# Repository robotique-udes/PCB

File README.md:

# PCB

Cette repo regroupe les fichiers et projets de PCB de tous les sous-groupe de robotique UdeS. Chaque groupe s'organise dans son dossier. Dans le futur il serait pertinent de monter une librairie de Symbole et de Footprint globale entre les groupes.

## Protection de branches:

- Seulement les branches nommées avec ce pattern sont acceptées:
  - rover/**
  - exo/**

- Une Pull Request est requise pour pouvoir merge dans le main

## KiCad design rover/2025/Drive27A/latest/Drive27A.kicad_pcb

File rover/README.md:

# PCB

Ce répertoire contient les projets du rover, les projets sont trié par version du rover:

| Compétition | Surnom du rover | Nom                                                |
|-------------|-----------------|----------------------------------------------------|
| CIRC 2024   | T_REX           | Teleoperated Rover for Extraterrestrial Xploration |

Les footprints custom locaux seront pour l'instant enregistrés à l'intérieur des projets pour simplifier la gestion. Dans le futur, une bibliothèque globale pourrait être créée.

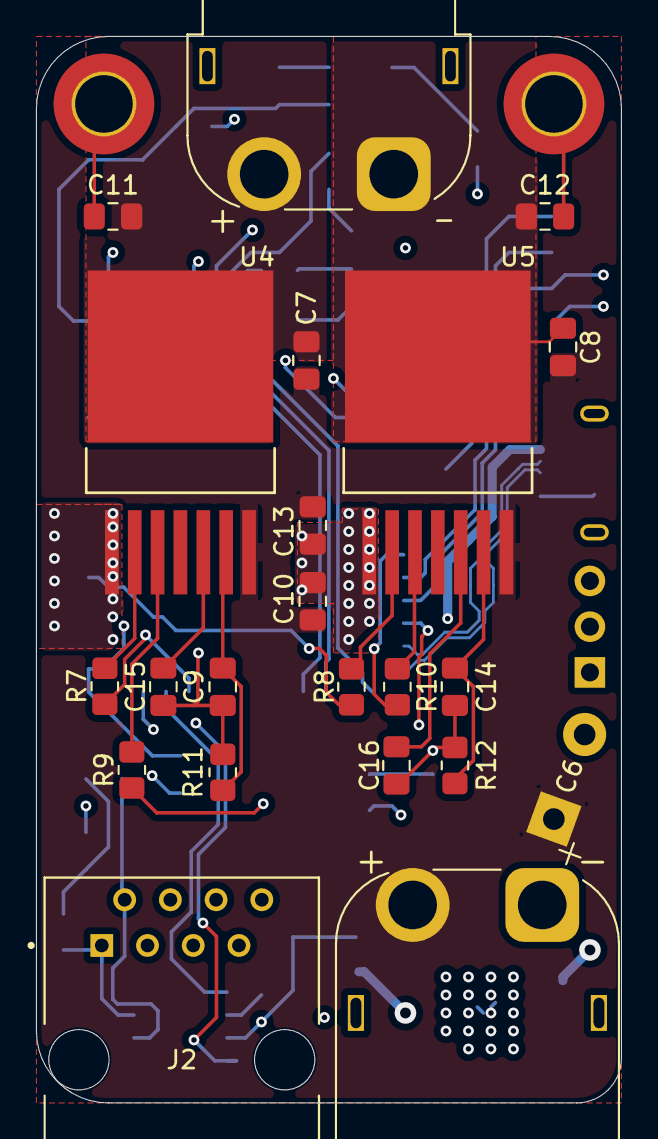
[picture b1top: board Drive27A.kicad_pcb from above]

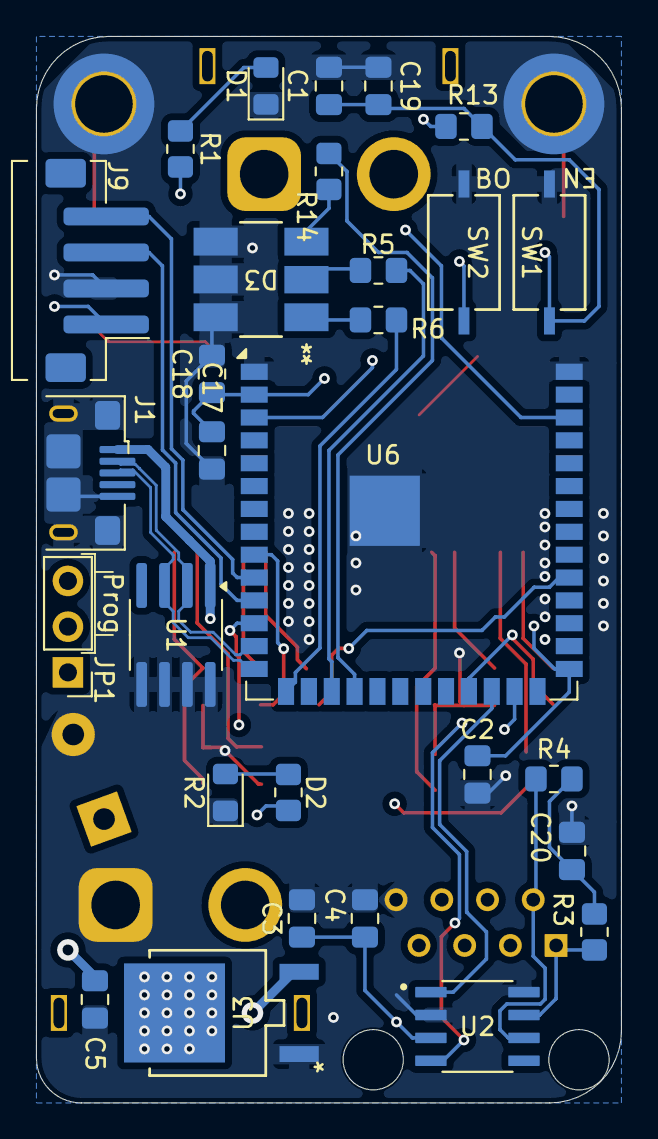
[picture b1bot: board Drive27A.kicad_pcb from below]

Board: 4 copper layers, 32.5 x 59.3 mm, 53 parts (29 on the bottom side), 40 nets.

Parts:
C1, C2, C4, C10, C13, C15, C16, C18: 100nF; C_0805_2012Metric_Pad1.18x1.45mm_HandSolder
C3, C5: 10uF; C_0805_2012Metric_Pad1.18x1.45mm_HandSolder
C6: 470uF; CP_Radial_D12.5mm_P5.00mm
C7, C8, C11, C12: 220nF; C_0805_2012Metric_Pad1.18x1.45mm_HandSolder
C9, C14: 1nF; C_0805_2012Metric_Pad1.18x1.45mm_HandSolder
C17: 22uF; C_0805_2012Metric_Pad1.18x1.45mm_HandSolder
C19: 1uF; C_0805_2012Metric_Pad1.18x1.45mm_HandSolder
C20: 47nF; C_0805_2012Metric_Pad1.18x1.45mm_HandSolder
D1, D2: R; LED_0805_2012Metric_Pad1.15x1.40mm_HandSolder
D3: CLP6C-FKB-CKNPRGJBB7A363; CLP6C-FKB-CKNPRGJBB7A363_CRE
H1, H2: MountingHole_Pad; MountingHole_3.2mm_M3_DIN965_Pad_TopBottom
J1: USB_B_Micro; USB_Micro-B_Amphenol_10118193-0001LF_Horizontal
J2: RJ45; AMPHENOL_54601-908WPLF
J6: XT60PW-M; AMASS_XT60PW-M_1x02_P7.20mm_Horizontal
J7: XT60PW-F; AMASS_XT60PW-F_1x02_P7.20mm_Horizontal
J9: B4B-XH-A_LF__SN_; JST_PH_B4B-PH-SM4-TB_1x04-1MP_P2.00mm_Vertical
JP1: Jumper_3_Open; PinHeader_1x03_P2.54mm_Vertical
R1, R2, R5, R6, R11, R12, R14: 1k; R_0805_2012Metric_Pad1.20x1.40mm_HandSolder
R3, R4: 60; R_0805_2012Metric_Pad1.20x1.40mm_HandSolder
R7, R8, R9, R10, R13: 10k; R_0805_2012Metric_Pad1.20x1.40mm_HandSolder
SW1, SW2: TS09-63-25-WT-160-SMT-TR; SW_TS09-63-25_CUD
U1: SOIC-8-1EP_3.9x4.9mm_P1.27mm_EP2.29x3mm
U2: SN65HVD232Q; SOIC127P600X175-8N
U3: LD1086DT33TR; TO252-2_AZ1117ID-3.3TRG1_DIO-L
U4, U5: BTN8962TA; PG-TO263-7-1_INF-M
U6: ESP32-S3-WROOM-1

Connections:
+3.3V: C3.1, C4.1, C17.1, C18.1, J9.1, R2.2, R13.1, U2.3 (VCC), U3.2 (OUTPUT), U6.2 (3V3)
+5V: J1.1 (VBUS), JP1.3 (B), U1.1
+24V: C6.1, C7.1, C8.1, C10.1, C13.1, J6.2 (+), U4.7 (VS), U5.7 (VS)
+24V_Logic: J2.7, JP1.1 (A)
CANH: J2.1, R3.2, U2.7 (CANH)
CANL: J2.2, R4.1, U2.6 (CANL)
ENC_QUAD_A: J9.3, U6.11 (IO18)
ENC_QUAD_B: J9.4, U6.10 (IO17)
EN_PB: C1.2, C19.1, R13.2, SW1.2, U6.3 (EN)
GND: C1.1, C2.1, C3.2, C4.2, C5.2, C6.2, C9.2, C10.2, C11.2, C12.2, C13.2, C14.2, C15.2, C16.2, C17.2, C18.2, C19.2, C20.1, D1.1 (K), D2.1 (K), D3.4, D3.5, D3.6, H1.1, H2.1, J1.5 (GND), J1.6 (Shield), J2.8, J6.1 (-), J9.2, R11.2, R12.2, SW1.1, SW2.1, U1.5, U1.6, U1.7, U1.8, U2.2 (GND), U2.8 (S), U3.1 (GND), U4.1 (GND), U5.1 (GND), U6.1 (GND), U6.40 (GND), U6.41 (GND)
GPIO_0: C2.2, SW2.2, U6.27 (IO0)
J2+: C7.2, C11.1, J7.2 (+), U4.8 (OUT)
J2-: C8.2, C12.1, J7.1 (-), U5.8 (OUT)
J2_EN_1: R9.2, U6.12 (IO8)
J2_EN_2: R10.2, U6.9 (IO16)
J2_IN_1: R7.2, U6.23 (IO21)
J2_IN_2: R8.2, U6.31 (IO38)
LED_B: R14.2, U6.18 (IO10)
LED_BUILDIN: R1.2, U6.38 (IO2)
LED_G: R5.2, U6.17 (IO9)
LED_R: R6.2, U6.15 (IO3)
unnamed: C20.2, R3.1, R4.2
unnamed: D1.2 (A), R1.1
unnamed: D2.2 (A), R2.1
unnamed: D3.1, R6.1
unnamed: D3.2, R5.1
unnamed: D3.3, R14.1
unnamed: C5.1, JP1.2 (C), U3.3 (INPUT)
unnamed: R9.1, U4.3 (EN_(INH))
unnamed: R7.1, U4.2 (IN)
unnamed: C9.1, R11.1, U4.6 (IS)
unnamed: C15.1, U4.5 (SR)
unnamed: R10.1, U5.3 (EN_(INH))
unnamed: R8.1, U5.2 (IN)
unnamed: C14.1, R12.1, U5.6 (IS)
unnamed: C16.1, U5.5 (SR)
RXC: U2.1 (TXD), U6.24 (IO47)
TXC: U2.4 (RXD), U6.25 (IO48)
USB_N: J1.2 (D-), U1.2, U6.13 (IO19)
USB_P: J1.3 (D+), U1.3, U6.14 (IO20)

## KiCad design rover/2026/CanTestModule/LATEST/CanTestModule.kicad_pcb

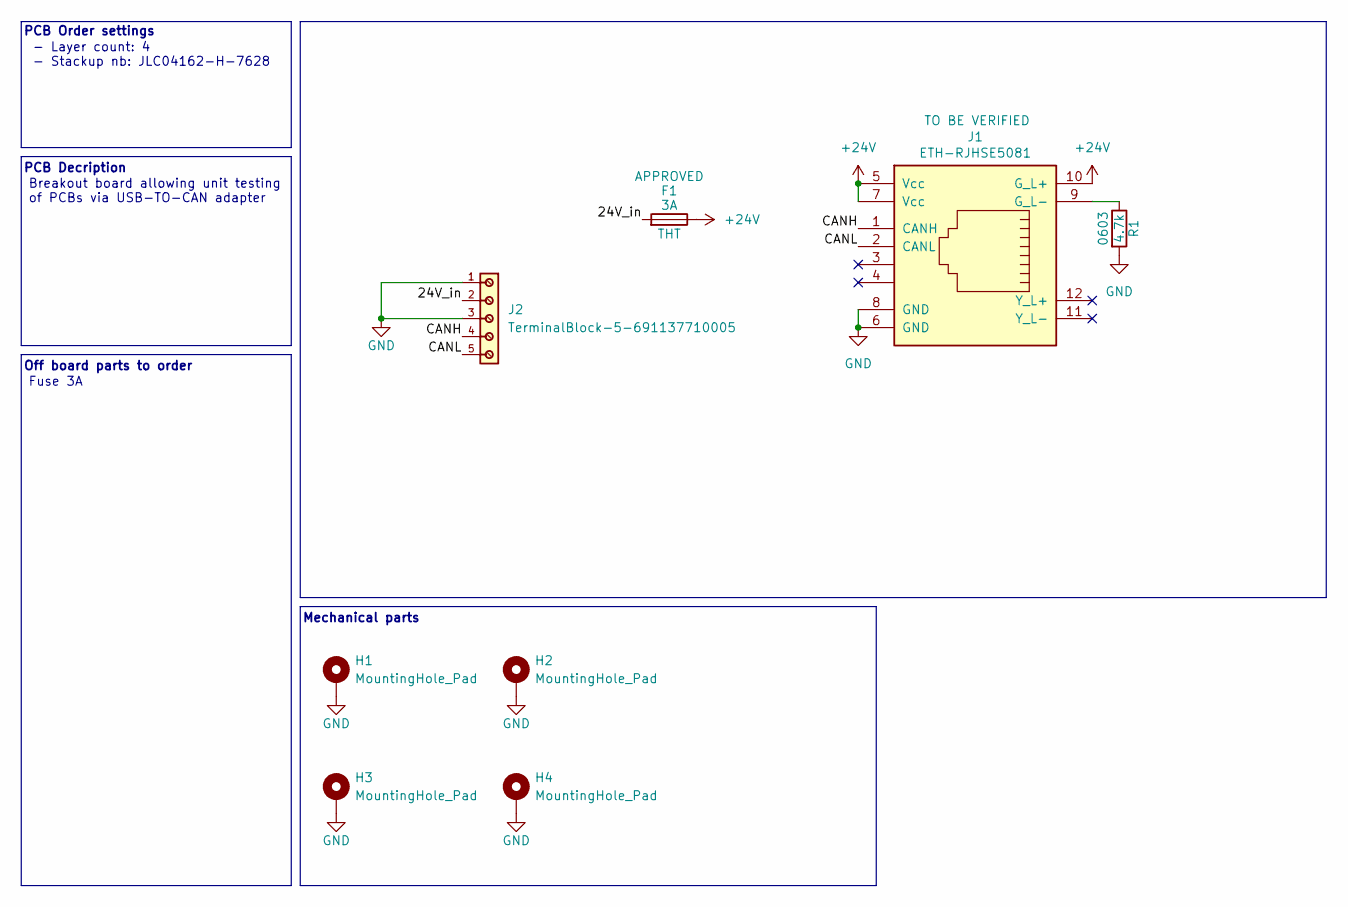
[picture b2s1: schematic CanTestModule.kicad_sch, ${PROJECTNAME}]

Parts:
F1: 3A; FUSE_3568-20
H1, H2, H3, H4: MountingHole_Pad; MountingHole_3.2mm_M3_DIN965_Pad_TopBottom
J1: ETH-RJHSE5081
J2: TerminalBlock-5-691137710005; TerminalBlock-5_P5.00mm-691137710005
R1: 4.7k; R_0603_1608Metric_Pad0.98x0.95mm_HandSolder

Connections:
+24V: F1.2, J1.5 (Vcc), J1.7 (Vcc), J1.10 (G_L+)
/24V_in: F1.1, J2.2
/CANH: J1.1 (CANH), J2.4
/CANL: J1.2 (CANL), J2.5
GND: H1.1 (1_1), H2.1 (1_1), H3.1 (1_1), H4.1 (1_1), J1.6 (GND), J1.8 (GND), J2.1, J2.3, R1.2
unnamed: J1.9 (G_L-), R1.1

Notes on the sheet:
Off board parts to order
Mechanical parts
- Layer count: 4 - Stackup nb: JLC04162-H-7628
PCB Decription
PCB Order settings
Breakout board allowing unit testing of PCBs via USB-TO-CAN adapter
Fuse 3A

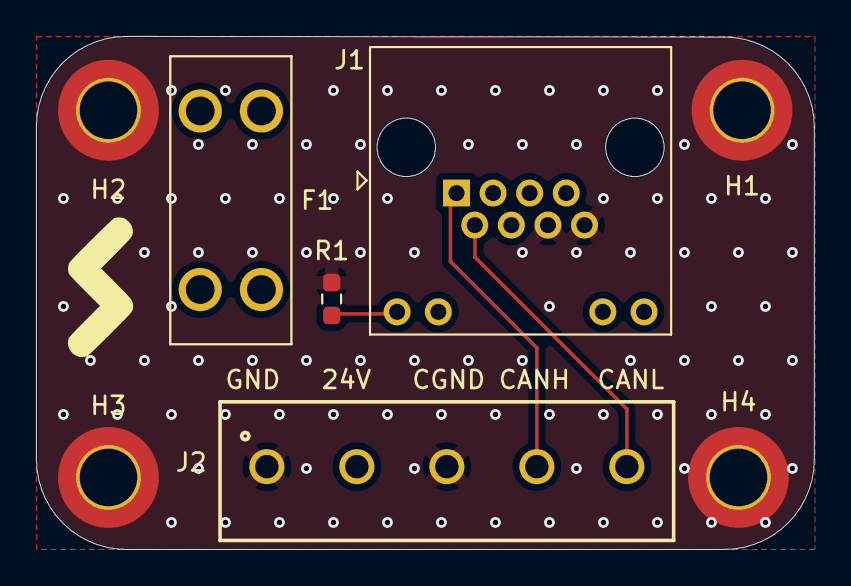
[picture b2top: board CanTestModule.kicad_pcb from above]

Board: 4 copper layers, 43.2 x 28.5 mm, 8 parts (0 on the bottom side), 6 nets.

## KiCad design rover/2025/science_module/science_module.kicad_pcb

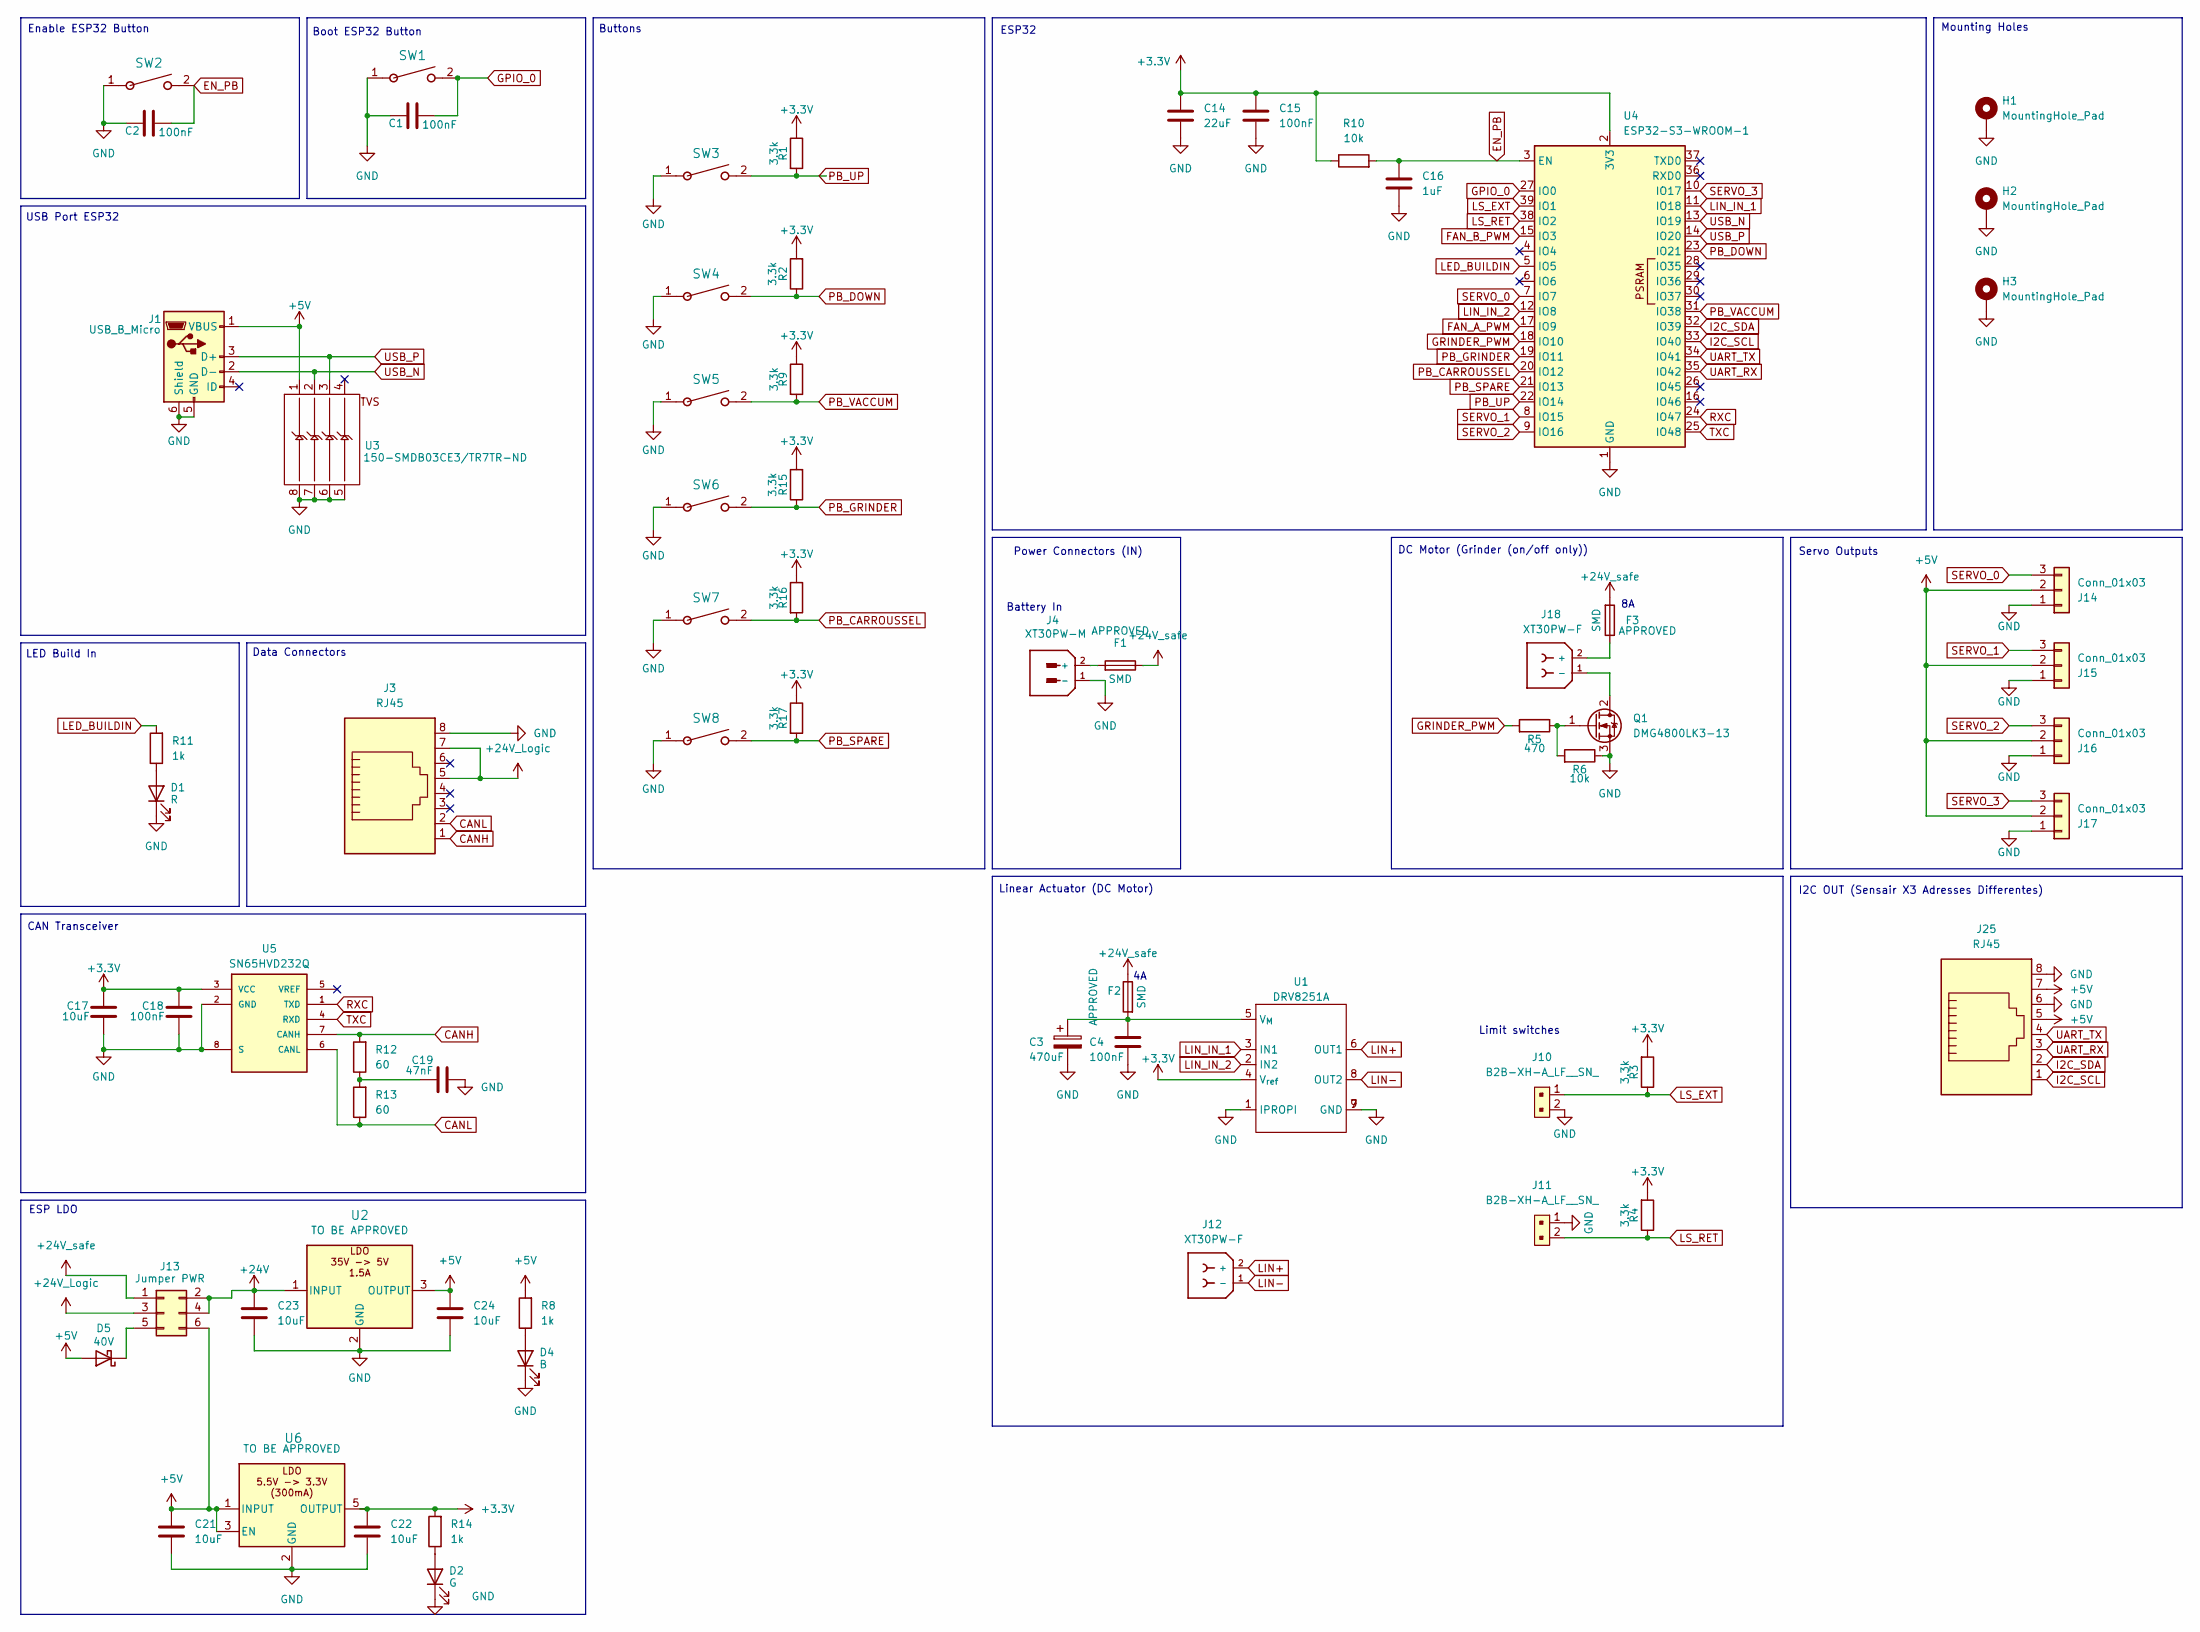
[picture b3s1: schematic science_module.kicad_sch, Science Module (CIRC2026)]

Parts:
C1, C2, C4, C15, C18: 100nF; C_0805_2012Metric_Pad1.18x1.45mm_HandSolder
C3: 470uF; CP_Radial_D8.0mm_P3.50mm
C14: 22uF; C_0805_2012Metric_Pad1.18x1.45mm_HandSolder
C16: 1uF; C_0805_2012Metric_Pad1.18x1.45mm_HandSolder
C17, C21, C22, C23, C24: 10uF; C_0805_2012Metric_Pad1.18x1.45mm_HandSolder
C19: 47nF; C_0805_2012Metric_Pad1.18x1.45mm_HandSolder
D1: R; LED_0805_2012Metric_Pad1.15x1.40mm_HandSolder
D2: G; LED_0805_2012Metric_Pad1.15x1.40mm_HandSolder
D4: B; LED_0805_2012Metric_Pad1.15x1.40mm_HandSolder
D5: 40V; D_SMA
F1, F2, F3: FuseHolder-3588-20
H1, H2, H3: MountingHole_Pad; MountingHole_3.2mm_M3_DIN965_Pad_TopBottom
J1: USB_B_Micro; USB_Micro-B_Amphenol_10118193-0001LF_Horizontal
J3, J25: RJ45; ASSMANN_A-2014-2-4-N-T-R
J4: XT30PW-M; AMASS_XT60PW-M_1x02_P7.20mm_Horizontal; PARTREV 1.2
J10, J11: B2B-XH-A_LF__SN_; JST_XH_B2B-XH-A_1x02_P2.50mm_Vertical; MPN B2B-XH-A(LF)(SN); Digi-Key_PN 455-2247-ND
J12, J18: XT30PW-F; AMASS_XT30PW-F_1x02_P2.50mm_Horizontal; PARTREV 1.2
J13: Jumper PWR; PinHeader_2x03_P2.54mm_Vertical
J14, J15, J16, J17: Conn_01x03; PinHeader_1x03_P2.54mm_Vertical
Q1: DMG4800LK3-13; TO-252-2
R1, R2, R3, R4, R9, R15, R16, R17: 3.3k; R_0805_2012Metric_Pad1.20x1.40mm_HandSolder
R5: 470; R_0805_2012Metric_Pad1.20x1.40mm_HandSolder
R6, R10: 10k; R_0805_2012Metric_Pad1.20x1.40mm_HandSolder
R8, R11, R14: 1k; R_0805_2012Metric_Pad1.20x1.40mm_HandSolder
R12, R13: 60; R_0805_2012Metric_Pad1.20x1.40mm_HandSolder
SW1, SW2, SW3, SW4, SW5, SW6, SW7, SW8: TS09-63-25-WT-160-SMT-TR; SW_TS09-63-25_CUD
U1: DRV8251A; Texas_HSOP-8-1EP_3.9x4.9mm_P1.27mm_ThermalVias
U2: LDO-LM7805MPX/NOPB; TO-263-3_TabPin2
U3: 150-SMDB03CE3/TR7TR-ND; SOIC-8-1EP_3.9x4.9mm_P1.27mm_EP2.29x3mm
U4: ESP32-S3-WROOM-1
U5: SN65HVD232Q; SOIC127P600X175-8N; PARTREV 4
U6: LDO-TLV74033PDBVR; SOT-23-5_HandSoldering

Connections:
+3.3V: C14.1, C15.1, C17.1, C18.1, C22.1, R1.1, R2.2, R3.2, R4.2, R9.1, R10.1, R14.2, R15.2, R16.1, R17.1, U1.4 (V_{ref}), U4.2 (3V3), U5.3 (VCC), U6.5 (OUTPUT)
+5V: C21.1, C24.1, D5.2 (A), J1.1 (VBUS), J13.6, J14.2, J15.2, J16.2, J17.2, J25.5, J25.7, R8.2, U2.3 (OUTPUT), U3.1, U6.1 (INPUT), U6.3 (EN)
+24V: C23.1, J13.2, J13.4, U2.1 (INPUT)
+24V_Logic: J3.5, J3.7, J13.3
+24V_safe: F1.2, F2.2, F3.1, J13.1
CANH: J3.1, R12.2, U5.7 (CANH)
CANL: J3.2, R13.1, U5.6 (CANL)
EN_PB: C2.2, C16.1, R10.2, SW2.2, U4.3 (EN)
FAN_A_PWM: U4.17 (IO9)
FAN_B_PWM: U4.15 (IO3)
GND: C1.1, C2.1, C3.2, C4.2, C14.2, C15.2, C16.2, C17.2, C18.2, C19.1, C21.2, C22.2, C23.2, C24.2, D1.1 (K), D2.1 (K), D4.1 (K), H1.1 (1_1), H2.1 (1_1), H3.1 (1_1), J1.5 (GND), J1.6 (Shield), J3.8, J4.1 (-), J10.2, J11.1, J14.1, J15.1, J16.1, J17.1, J25.6, J25.8, Q1.3 (S), R6.1, SW1.1, SW2.1, SW3.1, SW4.1, SW5.1, SW6.1, SW7.1, SW8.1, U1.1 (IPROPI), U1.7 (GND), U1.9 (GND), U2.2 (GND), U3.5, U3.6, U3.7, U3.8, U4.1 (GND), U4.40 (GND), U4.41 (GND), U5.2 (GND), U5.8 (S), U6.2 (GND)
GPIO_0: C1.2, SW1.2, U4.27 (IO0)
GRINDER_PWM: R5.2, U4.18 (IO10)
I2C_SCL: J25.1, U4.33 (IO40)
I2C_SDA: J25.2, U4.32 (IO39)
LED_BUILDIN: R11.2, U4.5 (IO5)
LIN+: J12.2 (+), U1.6 (OUT1)
LIN-: J12.1 (-), U1.8 (OUT2)
LIN_IN_1: U1.3 (IN1), U4.11 (IO18)
LIN_IN_2: U1.2 (IN2), U4.12 (IO8)
LS_EXT: J10.1, R3.1, U4.39 (IO1)
LS_RET: J11.2, R4.1, U4.38 (IO2)
unnamed: C19.2, R12.1, R13.2
unnamed: D1.2 (A), R11.1
unnamed: D2.2 (A), R14.1
unnamed: D4.2 (A), R8.1
unnamed: D5.1 (K), J13.5
unnamed: F1.1, J4.2 (+)
unnamed: F3.2, J18.2 (+)
unnamed: J18.1 (-), Q1.2 (D)
unnamed: Q1.1 (G), R5.1, R6.2
unnamed: C3.1, C4.1, F2.1, U1.5 (V_{M})
PB_CARROUSSEL: R16.2, SW7.2, U4.20 (IO12)
PB_DOWN: R2.1, SW4.2, U4.23 (IO21)
PB_GRINDER: R15.1, SW6.2, U4.19 (IO11)
PB_SPARE: R17.2, SW8.2, U4.21 (IO13)
PB_UP: R1.2, SW3.2, U4.22 (IO14)
PB_VACCUM: R9.2, SW5.2, U4.31 (IO38)
RXC: U4.24 (IO47), U5.1 (TXD)
SERVO_0: J14.3, U4.7 (IO7)
SERVO_1: J15.3, U4.8 (IO15)
SERVO_2: J16.3, U4.9 (IO16)
SERVO_3: J17.3, U4.10 (IO17)
TXC: U4.25 (IO48), U5.4 (RXD)
UART_RX: J25.3, U4.35 (IO42)
UART_TX: J25.4, U4.34 (IO41)
USB_N: J1.2 (D-), U3.2, U4.13 (IO19)
USB_P: J1.3 (D+), U3.3, U4.14 (IO20)

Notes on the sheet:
Boot ESP32 Button
LED Build In
Enable ESP32 Button
Servo Outputs
CAN Transceiver
I2C OUT (Sensair X3 Adresses Differentes)
Limit switches
DC Motor (Grinder (on/off only))
Power Connectors (IN)
ESP LDO
Buttons
Data Connectors
Mounting Holes
USB Port ESP32
Battery In
Linear Actuator (DC Motor)
ESP32

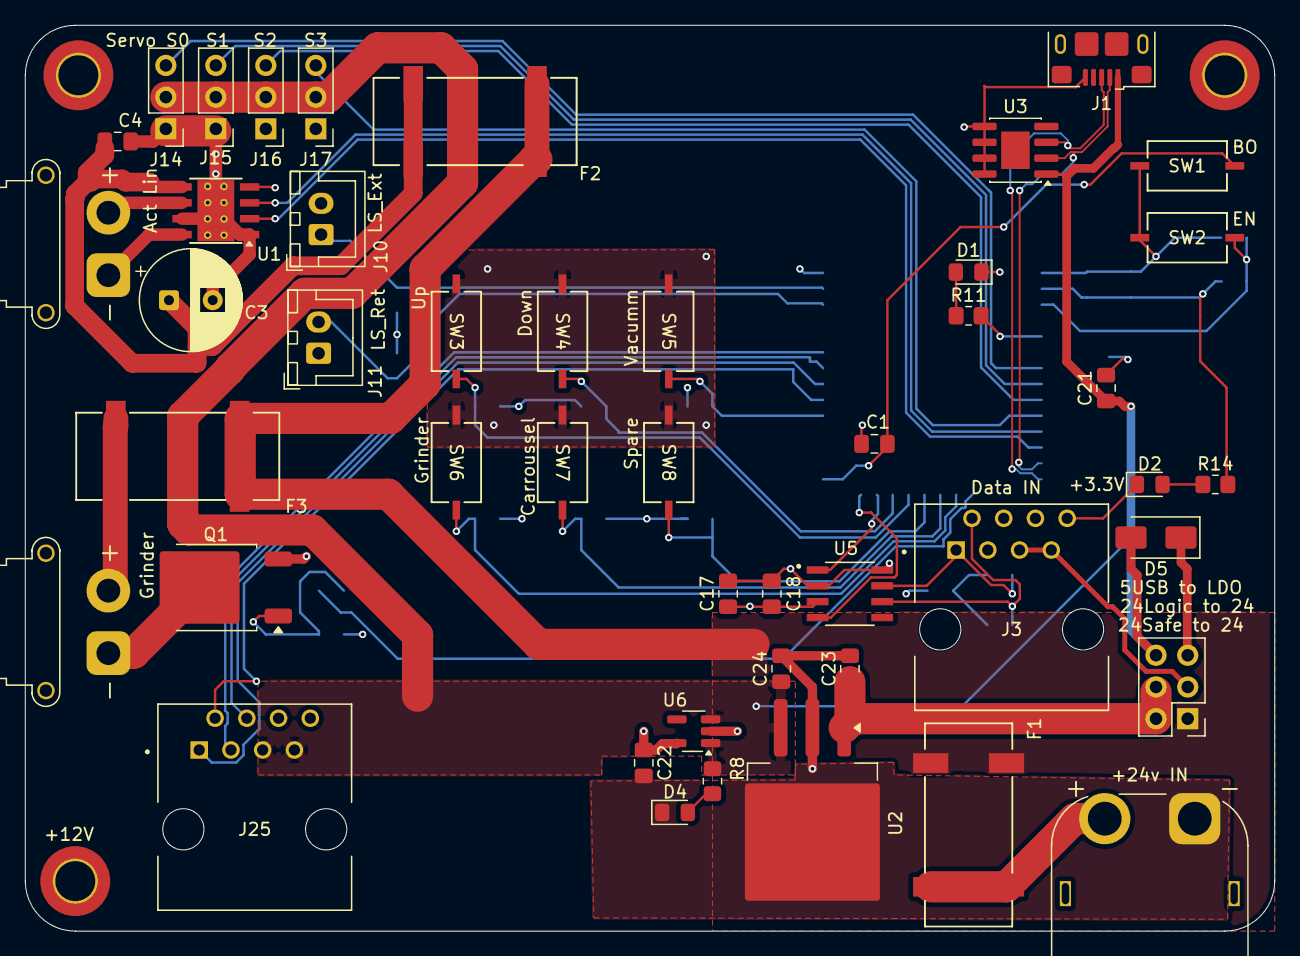
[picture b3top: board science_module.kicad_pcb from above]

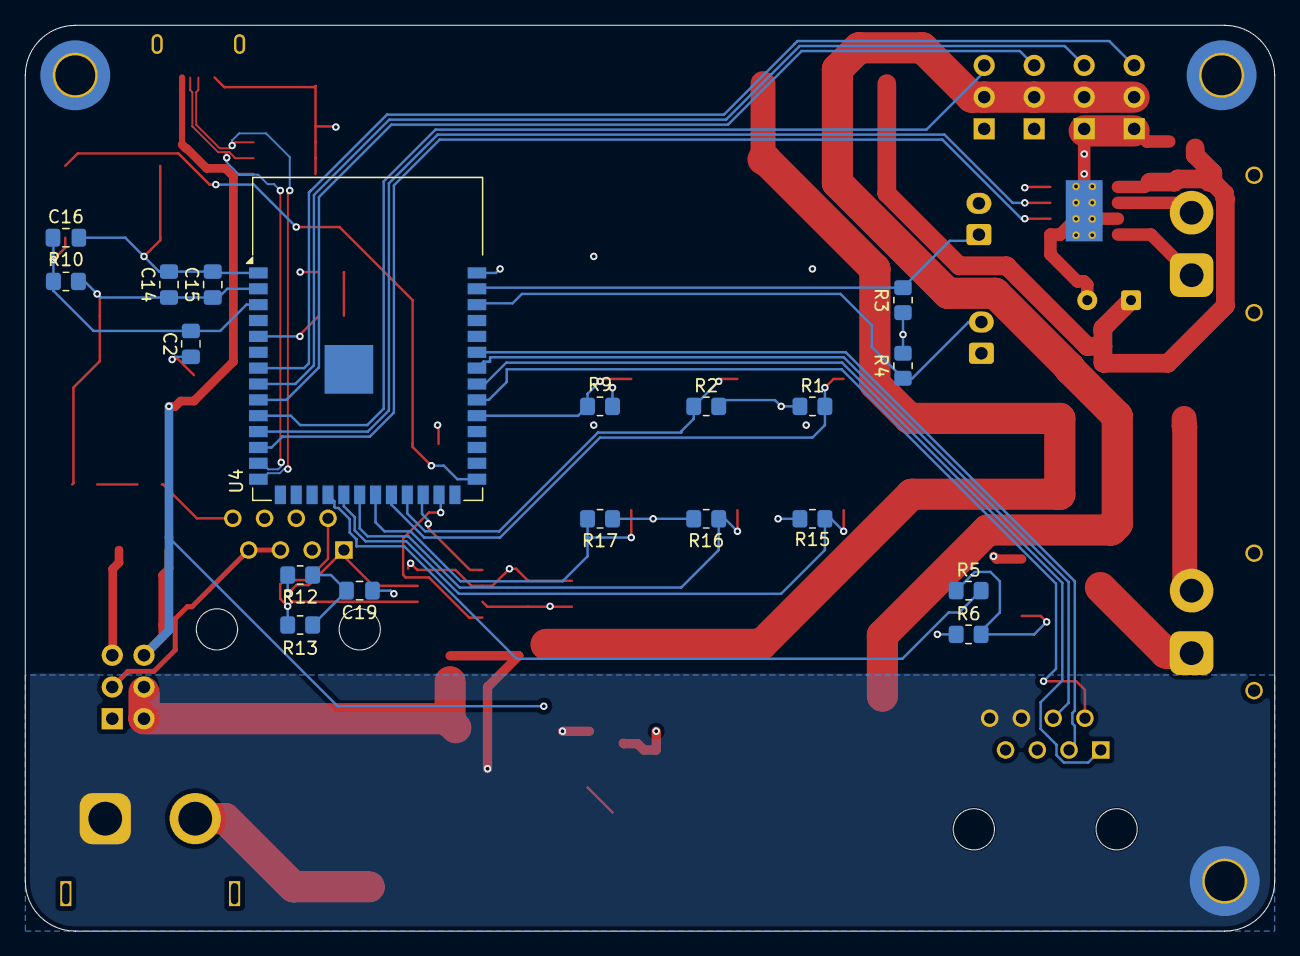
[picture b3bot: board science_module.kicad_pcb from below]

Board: 4 copper layers, 100.0 x 72.5 mm, 68 parts (19 on the bottom side), 46 nets.

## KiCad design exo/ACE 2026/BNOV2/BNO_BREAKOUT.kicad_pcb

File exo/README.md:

# PCB

Ce répertoire contient les projets de BioGenius, les projets sont trié par version du rover:

| Compétition | Nom          |  Description                                          |
|-------------|--------------|-------------------------------------------------------|
| ACE 2023    | Darianne     | Exo léger, 1st place ACE 2023                         |
| ACE 2024    | Biggy (?)    | Exo avec support a bonbonne de pompier, 3rd place     |
| ACE 2025    | TBD          |                                                       |

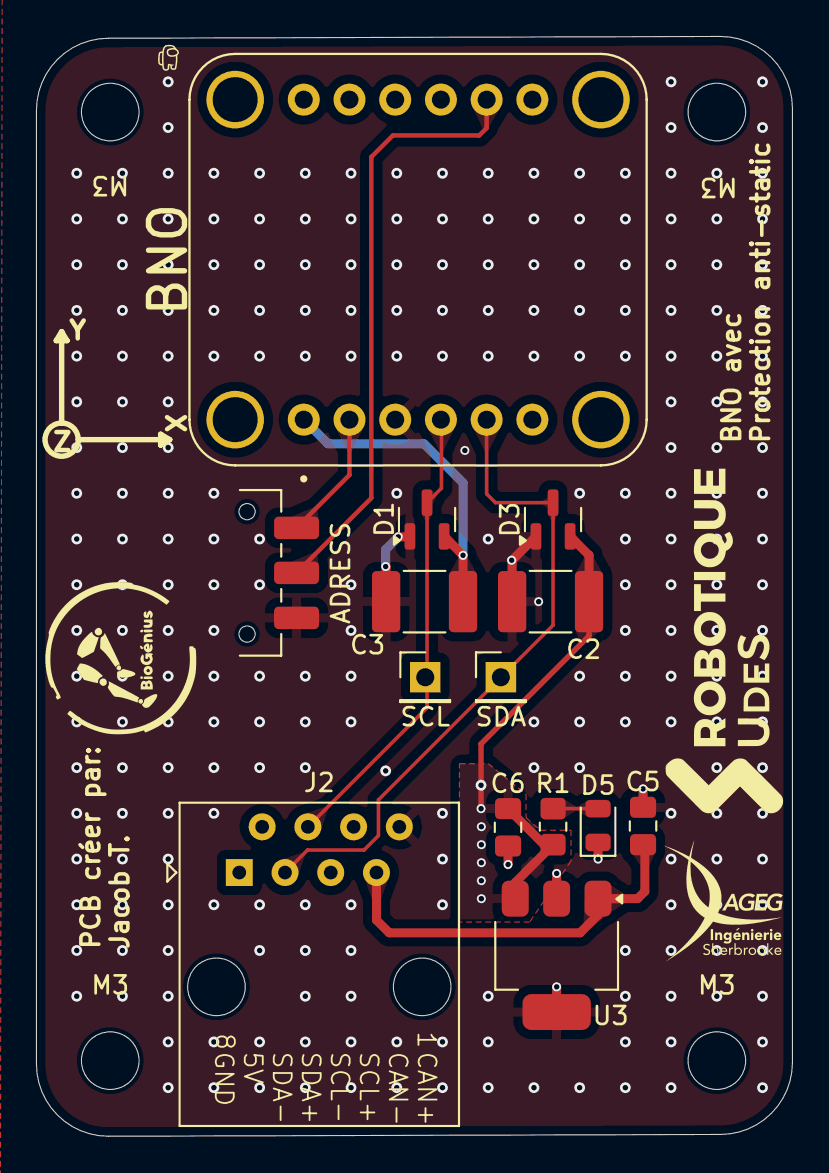
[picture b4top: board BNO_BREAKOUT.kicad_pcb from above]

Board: 2 copper layers, 42.0 x 61.1 mm, 16 parts (0 on the bottom side), 8 nets.

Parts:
ADRESS: SW_SPDT; SW_SPDT_CK_JS102011SAQN
BNO: 4754; MODULE_4754
C2, C3: 1n; C_1812_4532Metric_Pad1.57x3.40mm_HandSolder
C5, C6: 4,7µF; C_0805_2012Metric_Pad1.18x1.45mm_HandSolder
D1, D3: BAV99; SOT-23
D5: Green_power; D_0805_2012Metric
J2: RJ45; RJ45_Amphenol_54602-x08_Horizontal
M3, M3#2: MountingHole_3.2mm_M3
R1: 330; R_0805_2012Metric_Pad1.20x1.40mm_HandSolder
SCL: SCL; PinHeader_1x01_P2.54mm_Vertical
SDA: SDA; PinHeader_1x01_P2.54mm_Vertical
U3: AP7361C-33E; SOT-223-3_TabPin2

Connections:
/3V3: BNO.JP1_1 (VIN), C2.1, C3.1, C6.2, D1.2 (A), D3.2 (A), R1.1, U3.3 (VO)
/5V: C5.2, J2.7, U3.1 (VI)
/SCL: BNO.JP1_4 (SCL), D1.3 (K), J2.4, SCL.1
/SDA: BNO.JP1_5 (SDA), D3.3 (K), J2.3, SDA.1
GND: ADRESS.3 (C), BNO.JP1_3 (GND), C2.2, C3.2, C5.1, C6.1, D1.1 (K), D3.1 (K), D5.1 (K), J2.8, U3.2 (GND)
unnamed: D5.2 (A), R1.2
unnamed: ADRESS.1 (A), BNO.JP1_2 (3VO)
unnamed: ADRESS.2 (B), BNO.JP2_5 (DI)

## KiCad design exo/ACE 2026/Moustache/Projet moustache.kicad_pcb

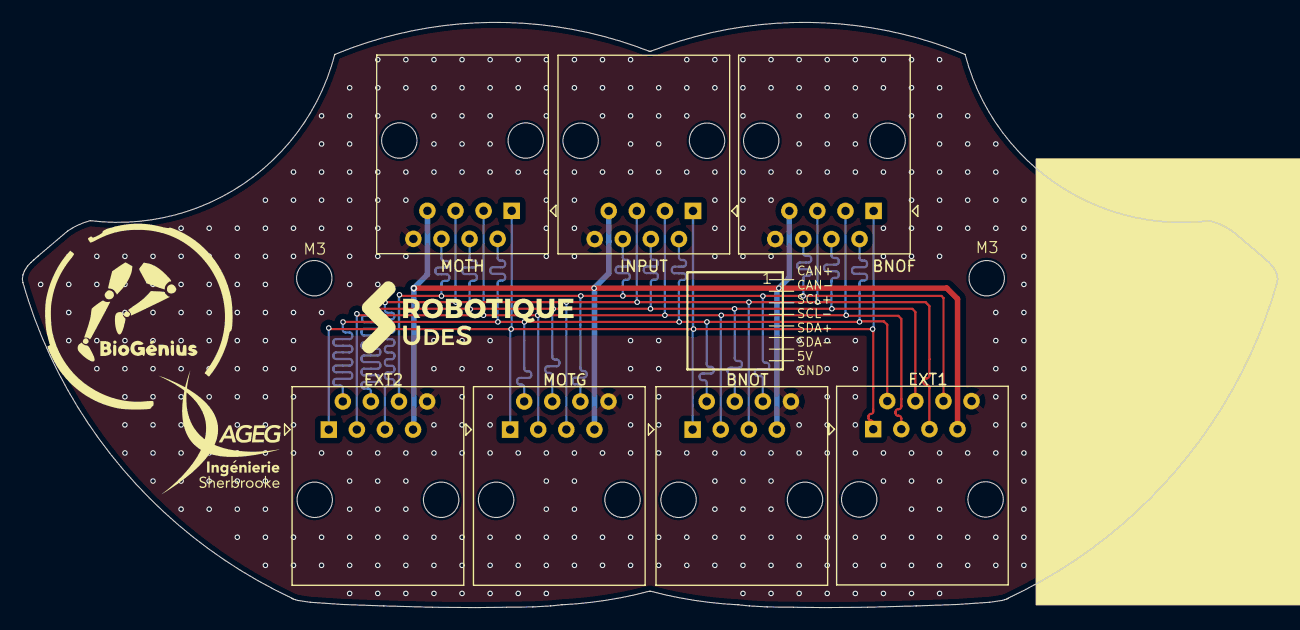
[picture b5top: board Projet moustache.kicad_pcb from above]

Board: 2 copper layers, 113.5 x 52.9 mm, 9 parts (0 on the bottom side), 8 nets.

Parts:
BNOF: RJ45; RJ45_Amphenol_54602-x08_Horizontal
BNOT: RJ45; RJ45_Amphenol_54602-x08_Horizontal
EXT1, EXT2: RJ45; RJ45_Amphenol_54602-x08_Horizontal
H1, H2: MountingHole; MountingHole_3.2mm_M3
INPUT: RJ45; RJ45_Amphenol_54602-x08_Horizontal
MOTG: RJ45; RJ45_Amphenol_54602-x08_Horizontal
MOTH: RJ45; RJ45_Amphenol_54602-x08_Horizontal

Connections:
+5V: BNOF.7, BNOT.7, EXT1.7, EXT2.7, INPUT.7, MOTG.7, MOTH.7
/CAN+: BNOF.1, BNOT.1, EXT1.1, EXT2.1, INPUT.1, MOTG.1, MOTH.1
/CAN-: BNOF.2, BNOT.2, EXT1.2, EXT2.2, INPUT.2, MOTG.2, MOTH.2
/SCL+: BNOF.3, BNOT.3, EXT1.3, EXT2.3, INPUT.3, MOTG.3, MOTH.3
/SCL-: BNOF.4, BNOT.4, EXT1.4, EXT2.4, INPUT.4, MOTG.4, MOTH.4
/SDA+: BNOF.5, BNOT.5, EXT1.5, EXT2.5, INPUT.5, MOTG.5, MOTH.5
/SDA-: BNOF.6, BNOT.6, EXT1.6, EXT2.6, INPUT.6, MOTG.6, MOTH.6
GND: BNOF.8, BNOT.8, EXT1.8, EXT2.8, INPUT.8, MOTG.8, MOTH.8

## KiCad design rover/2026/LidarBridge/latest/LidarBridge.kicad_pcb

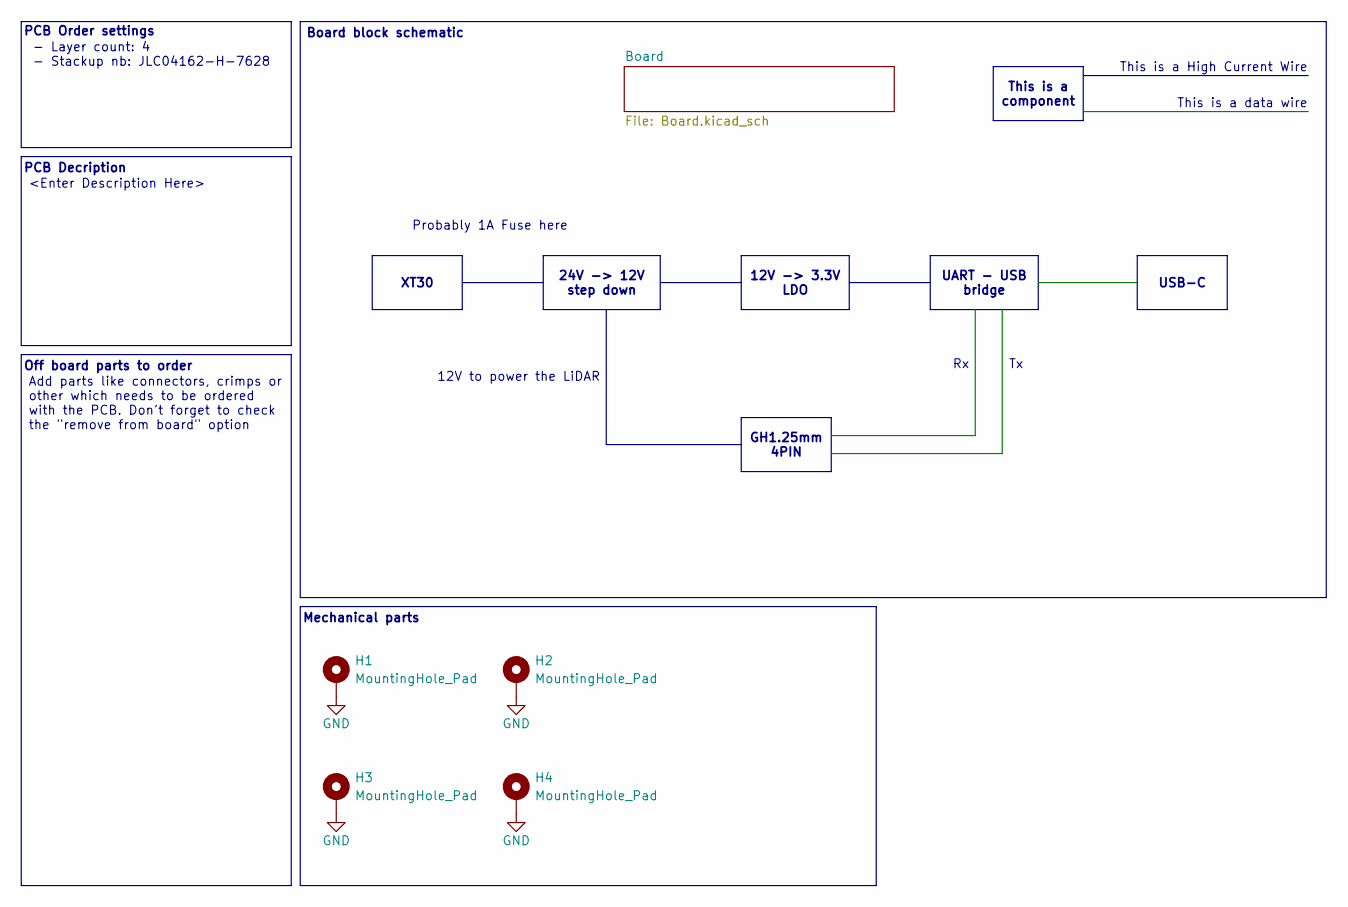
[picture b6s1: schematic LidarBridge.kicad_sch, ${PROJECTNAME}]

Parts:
H1, H2, H3, H4: MountingHole_Pad; MountingHole_3.2mm_M3_DIN965_Pad_TopBottom

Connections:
GND: H1.1, H2.1, H3.1, H4.1; also elsewhere on the board

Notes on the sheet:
Off board parts to order
Mechanical parts
- Layer count: 4 - Stackup nb: JLC04162-H-7628
This is a data wire
PCB Decription
Probably 1A Fuse here
12V to power the LiDAR
Board block schematic
This is a High Current Wire
PCB Order settings
XT30
USB-C
GH1.25mm 4PIN
UART - USB bridge
<Enter Description Here>
Add parts like connectors, crimps or other which needs to be ordered with the PCB. Don't forget to check the "remove from board" option
12V -> 3.3V LDO
This is a component
24V -> 12V step down
